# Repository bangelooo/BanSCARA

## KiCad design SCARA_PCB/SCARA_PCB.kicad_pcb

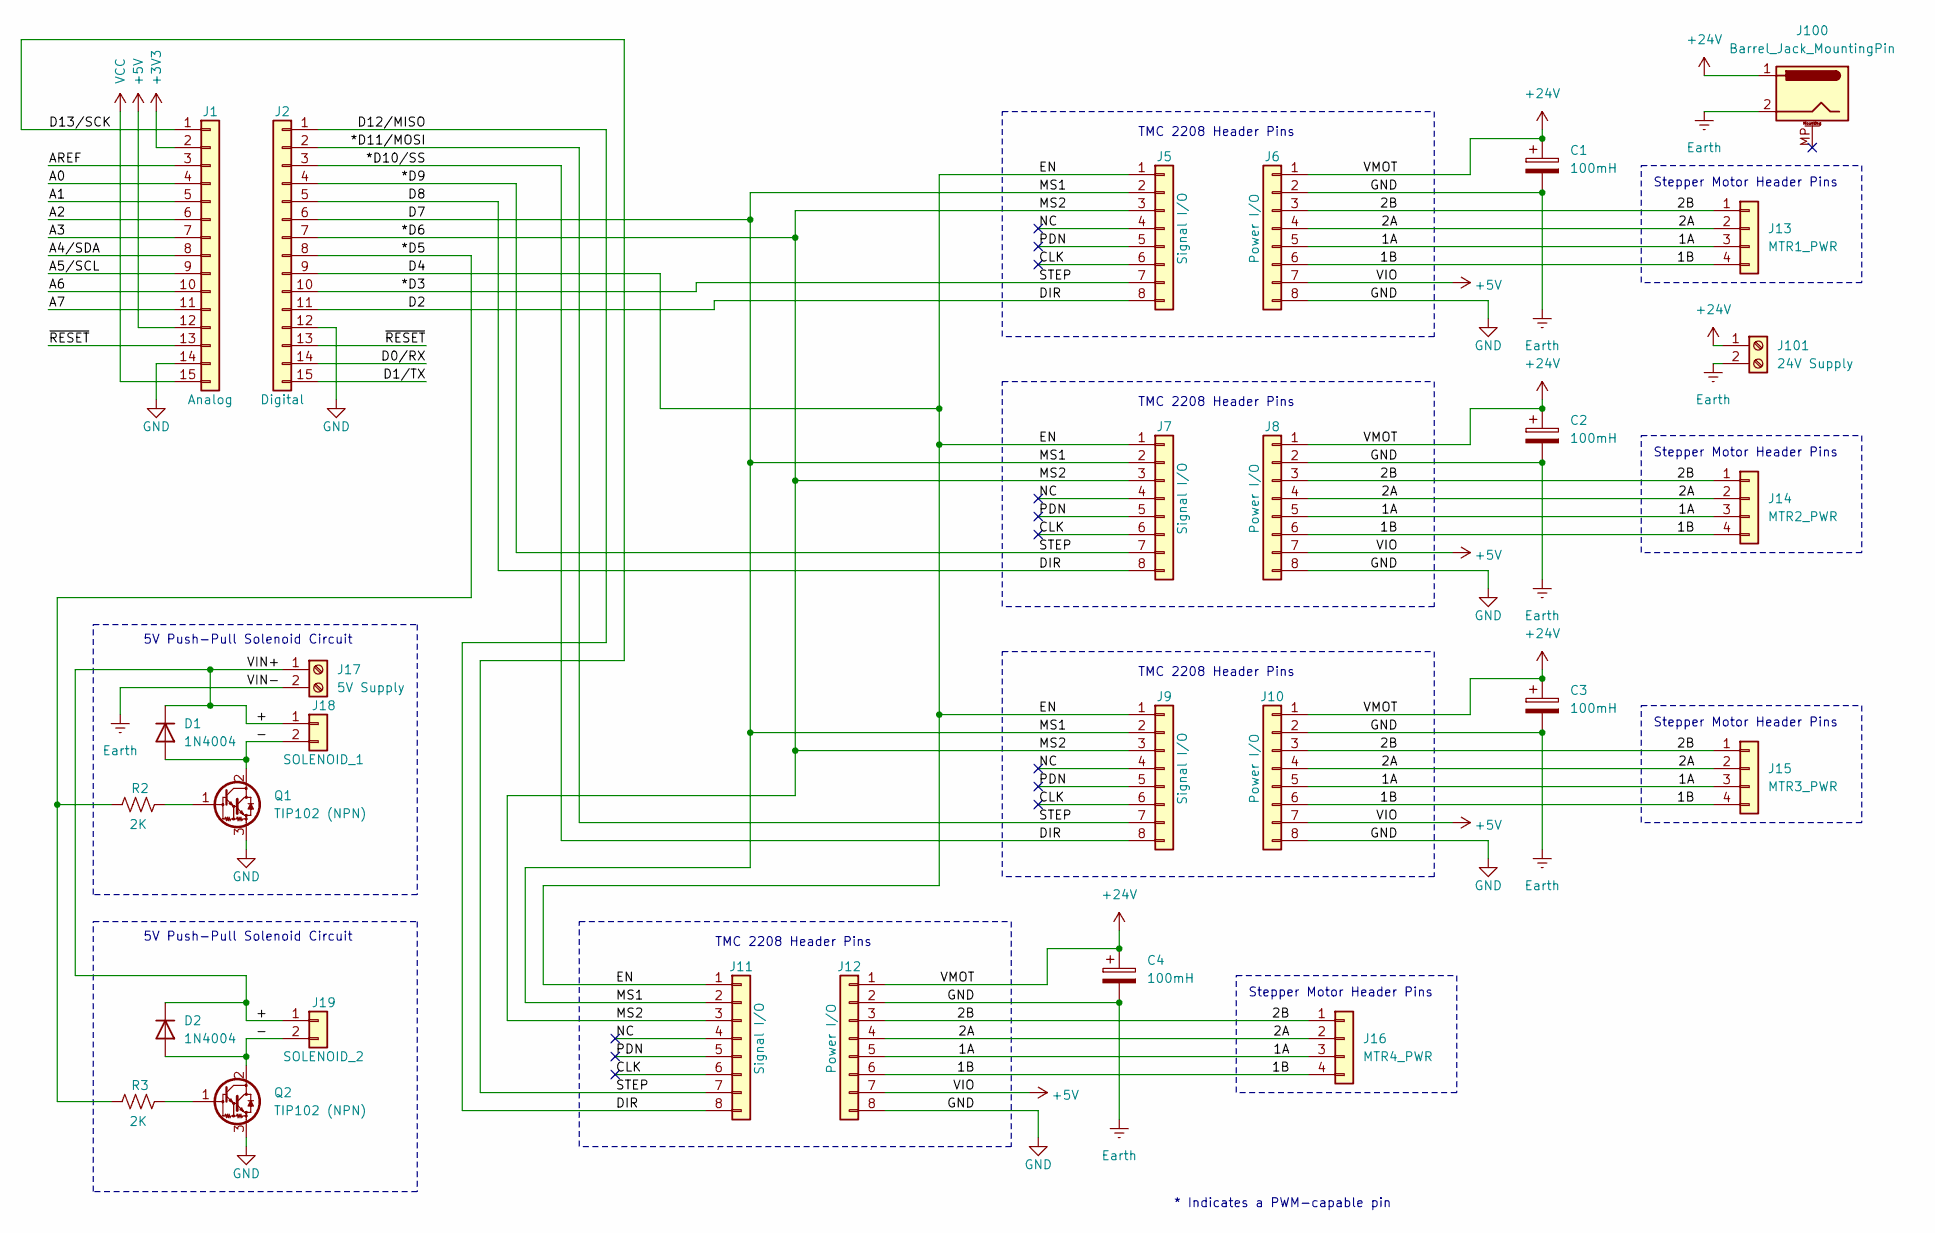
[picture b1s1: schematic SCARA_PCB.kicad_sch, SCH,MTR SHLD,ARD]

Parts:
C1, C2, C3, C4: 100mH
D1, D2: 1N4004
J1: Analog; PinSocket_1x15_P2.54mm_Vertical
J2: Digital; PinSocket_1x15_P2.54mm_Vertical
J5, J7, J9, J11: Signal I/O; PinSocket_1x08_P2.54mm_Vertical
J6, J8, J10, J12: Power I/O; PinSocket_1x08_P2.54mm_Vertical
J13: MTR1_PWR
J14: MTR2_PWR
J15: MTR3_PWR
J16: MTR4_PWR
J17: 5V Supply
J18: SOLENOID_1
J19: SOLENOID_2
J100: Barrel_Jack_MountingPin; BarrelJack_CUI_PJ-102AH_Horizontal
J101: 24V Supply
Q1, Q2: TIP102 (NPN); TO-220-3_Vertical
R2, R3: 2K

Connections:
+3V3: J1.2
+5V: J1.12, J6.7, J8.7, J10.7, J12.7
+24V: C1.1, C2.1, C3.1, C4.1, J6.1, J8.1, J10.1, J12.1, J100.1, J101.1
/1A: J6.5, J8.5, J10.5, J12.5, J13.3, J14.3, J15.3, J16.3
/1B: J6.6, J8.6, J10.6, J12.6, J13.4, J14.4, J15.4, J16.4
/2A: J6.4, J8.4, J10.4, J12.4, J13.2, J14.2, J15.2, J16.2
/2B: J6.3, J8.3, J10.3, J12.3, J13.1, J14.1, J15.1, J16.1
/*D5: J2.8, R2.2, R3.2
/*D6: J2.7, J5.3, J7.3, J9.3, J11.3
/*D10/SS: J2.1, J2.3, J2.5, J2.11, J5.8, J7.8, J9.8, J11.8
/*D11/MOSI: J1.1, J2.2, J2.4, J2.10, J5.7, J7.7, J9.7, J11.7
/+: D1.1 (K), D2.1 (K), J17.1, J18.1, J19.1
/-: D1.2 (A), D2.2 (A), J18.2, J19.2, Q1.2 (C), Q2.2 (C)
/A0: J1.4
/A1: J1.5
/A2: J1.6
/A3: J1.7
/A4/SDA: J1.8
/A5/SCL: J1.9
/A6: J1.10
/A7: J1.11
/AREF: J1.3
/CLK: J5.6, J7.6, J9.6, J11.6
/D0/RX: J2.14
/D1/TX: J2.15
/D4: J2.9, J5.1, J7.1, J9.1, J11.1
/D7: J2.6, J5.2, J7.2, J9.2, J11.2
/NC: J5.4, J7.4, J9.4, J11.4
/PDN: J5.5, J7.5, J9.5, J11.5
/~RESET: J1.13, J2.13
Earth: C1.2, C2.2, C3.2, C4.2, J1.14, J2.12, J6.2, J6.8, J8.2, J8.8, J10.2, J10.8, J12.2, J12.8, J17.2, J100.2, J101.2, Q1.3 (E), Q2.3 (E)
unnamed: Q1.1 (B), R2.1
unnamed: Q2.1 (B), R3.1
VCC: J1.15

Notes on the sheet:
TMC 2208 Header Pins
5V Push-Pull Solenoid Circuit
Stepper Motor Header Pins
* Indicates a PWM-capable pin

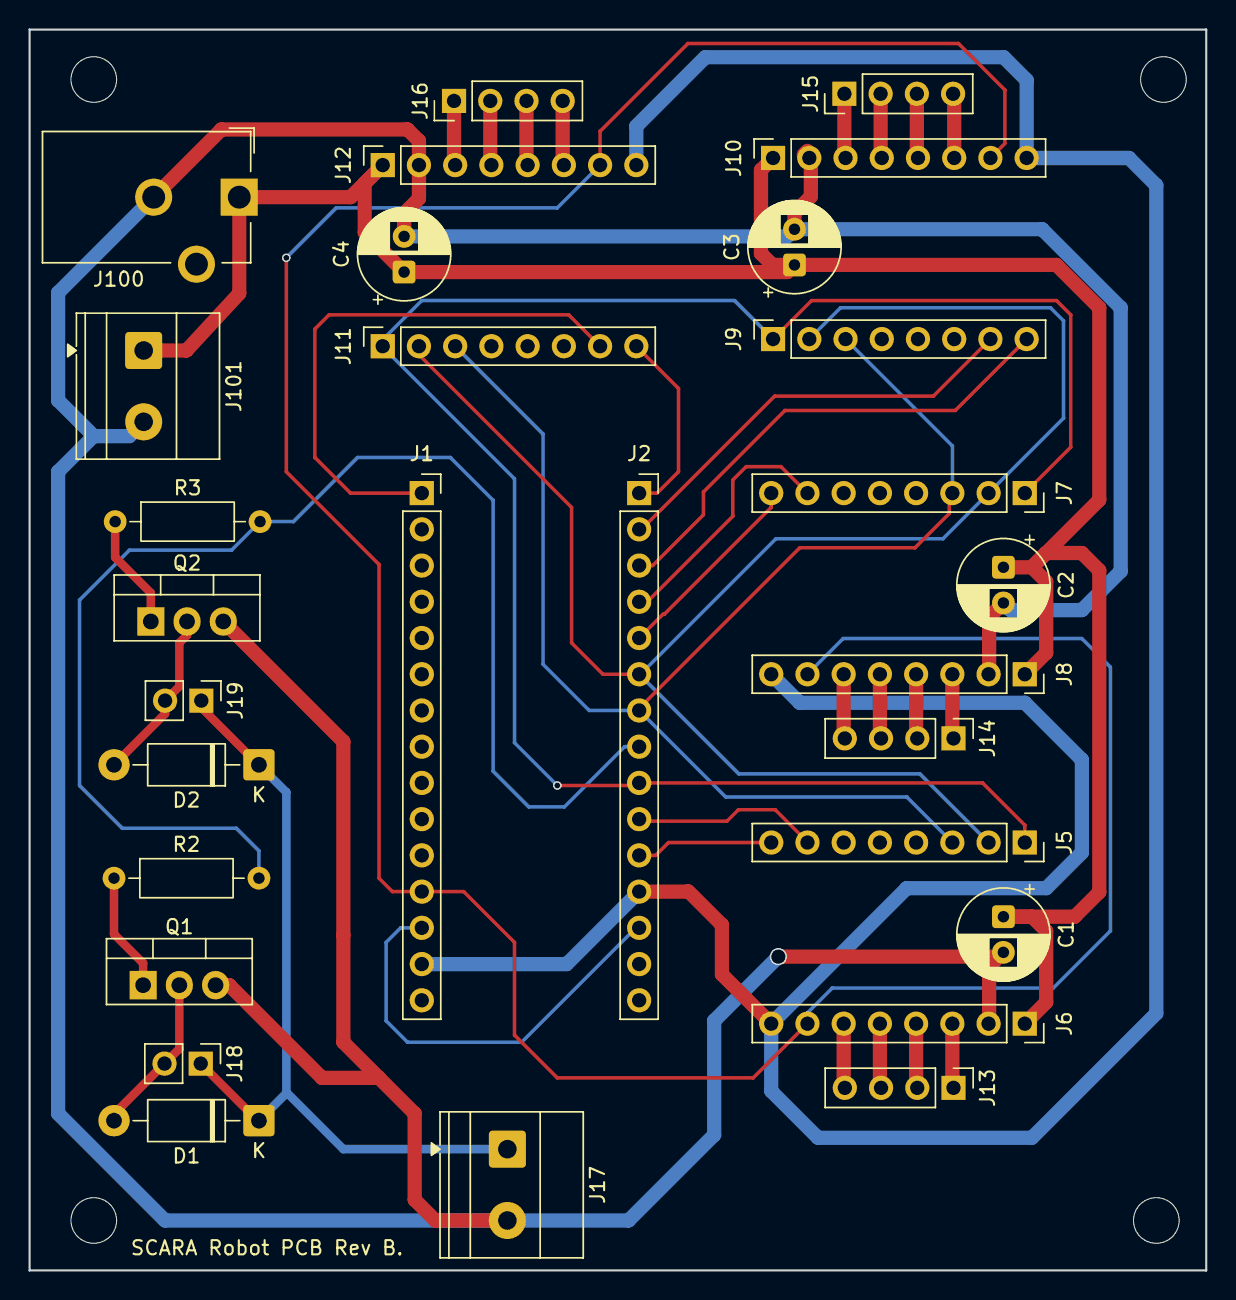
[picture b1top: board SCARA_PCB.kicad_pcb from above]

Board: 2 copper layers, 82.5 x 87.0 mm, 33 parts (0 on the bottom side), 21 nets.

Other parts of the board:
MH1, MH2, MH3, MH4: MountingHole_3.2mm

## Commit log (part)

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2025-05-27 Single stepper motor control
2025-06-02 Code for controlling two stepper motors. Need to fix cycling.
    Cycling currently repeats 5 times, twice.
2025-06-11 Forward kinematics for SCARA robot.
    The forward kinematics for this SCARA robot was developed using the Elementary Transformation Sequence (ETS) proposed by Peter Corke. The code will have to be modified to fully function in the Arduin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
    main.cpp in the Backup folder has both the ET and ETS classes included.
2025-08-02 SCARA Controller Version 0.1
    The user has the ability to send string commands to control 3 joints of the SCARA robot. The moves available are relative and absolute. Q1 = Z-axs, Q2 = Revolute Joint 1, Q2 = Revolute Joint 2.
    A string parse function is used set command positions.
    Current version does not support velocity setpoints.
    Known Issue: After performing relative move, the robot will move to its absolute position if an ABS move is called and the robot joint is not called.
2025-09-13 Initial Python class for the banSCARA robot.
2025-09-22 Symbolic robot class.
2025-12-13 New classes, updates to main, and new methods
    Methods:
    1. FK
    2. IK
    3. animateTraj
    Classes:
    1. robotLink
2025-12-23 Fix single axis relative move commands
    After relative move is complete, the motor will go back to last absolute position if ABS is commanded.
    This problem has been resolved for a single axis, but commanding multiple axis moves causes all motors to repeat the relative moves
2025-12-23 Latest robotArmClass. Slightly updated IK and more detail on animation method
2025-12-24 Fix relative move so it does not repeat unless a new command has been issued.
2026-01-03 Re-orgnize class. Include Robot Pose Info
    Added class attributes and methods to update the robot's pose after a joint update.
2026-01-04 First Draft of GUI using PyQt6
    First draft of GUI using PyQt6.
2026-01-04 Re-orginize file structure. Add more functionality to GUI. Add PubSub architecture.
2026-01-13 Add methods to calculate spatial and body jacobians. Add description to RobotArm class methods
    Add methods to calculate spatial and body jacobians. Add description to RobotArm class methods
2026-01-27 Trajectory Planning
    Cubic Polynomial, Linear with Parabolic Blend (Time Specification), Trapezoidal Trajectory (Velocity and Motion Rule specification)
2026-02-01 Clean up CustomLibraries Folder.
    Consolidate RobotArm,RobotLink, and RobotArmController Classes into one module.
    Consolidate PubSub and ActionClientServer classes into one module.
2026-02-10 Update Robot Communications module.
    Add Action Client and Action Server classes. Can send goals, provide feedback, get results back after goal completion.
2026-02-16 Update RobotGUI, RobotCommunications, RobotArmLibrary, and Trajectory Plaanning
    Fix logic in RobotGUI,RobotCommunications,RobotArmLibrary, and TrajectoryPlanning modules.
2026-02-28 Add 4th motor. Add motor on and motor off logic.
2026-03-01 Update homing/calibration/indexing logic and velocity move logic
2026-03-08 Add Direct homing/calibration/indexing feature on GUI,Controller, and Arduino
2026-03-30 Add End Effector Gripping Function (preliminary)
    - Update Arduino Code, GUI Code, and Controller Code to perfrom internal gripping operation.
2026-03-30 Release Object Functionality (Preliminary)
    Update Arduino, GUI and Controller for Object Release Functionality (Minimal)
2026-04-02 Fix logic
2026-04-03 Feature: LED Color during Indexing/Calibration/Homing
2026-04-04 Add relative movements for CAM class
2026-04-04 Correct Q1 absolute and relative moves in Joint Space.
2026-04-04 Correct Cartesian Space Commands
    Can now command and jog all axes in Cartesian Space
2026-04-11 Add ACK/NACK to Arduino. Update send() method in RobotController.
2026-04-14 Grip diameter publisher/subscriber added to GUI. Added default routine for robotController class.
    Updated Action Client for thread safety. Can now create a C-Space routine for the robot without race conditions.
2026-04-16 Add place logic to robotController.
2026-05-10 Computer Vision Learnings - Color Detection
    Example of color detection using OpenCV.
